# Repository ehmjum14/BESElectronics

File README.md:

# BESElectronics
Electronic part of the BESDyno diploma thesis
 - [Software part by Emil Berger](https://github.com/beremm14/BESDyno)

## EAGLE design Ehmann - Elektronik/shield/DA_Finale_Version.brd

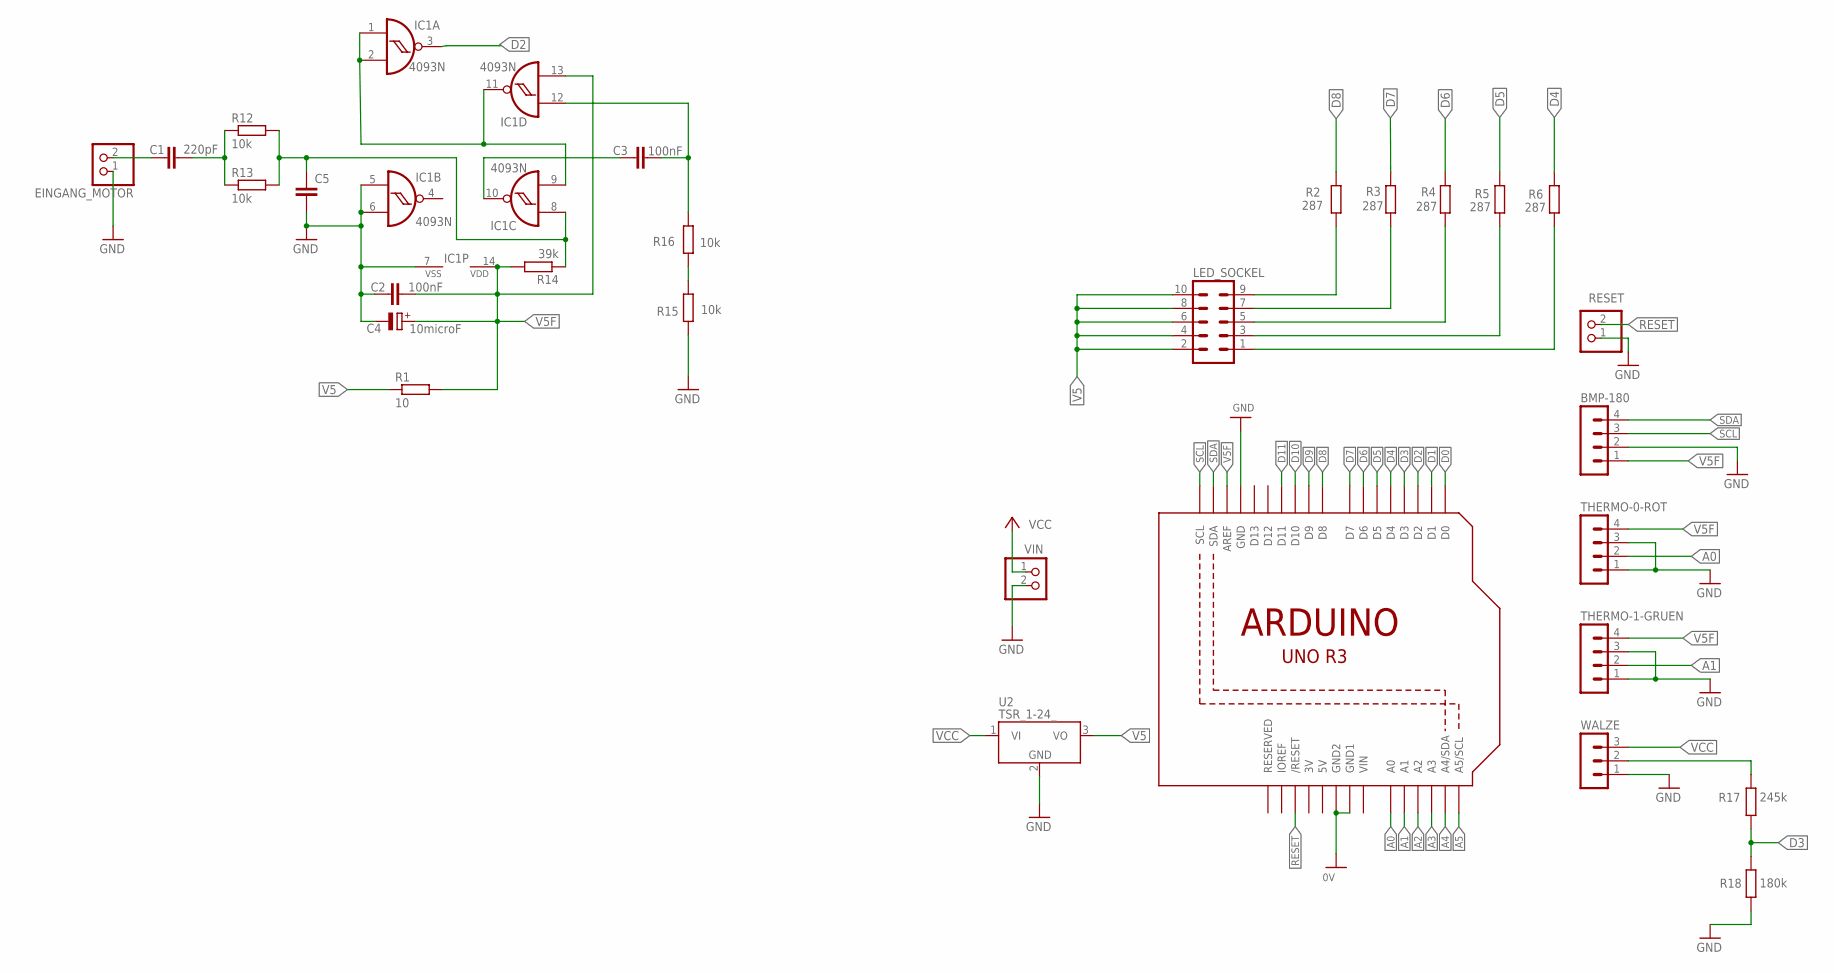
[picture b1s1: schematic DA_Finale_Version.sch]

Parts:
BMP-180: MA04-1
C1: 220pF; C050-025X075
C2, C3: 100nF; C050-025X075
C4: 10microF; E3,5-8
C5: C-EU050-025X075; C050-025X075
EINGANG_MOTOR: PINHD-1X2; 1X02
IC1: 4093N; DIL14
LED_SOCKEL: MA05-2
R1: 10; 0207/7
R2, R3, R4, R5, R6: 287; 0207/10
R12, R13, R15, R16: 10k; 0207/7
R14: 39k; 0207/7
R17: 245k; 0207/7
R18: 180k; 0207/7
RESET: PINHD-1X2; 1X02
THERMO-0-ROT, THERMO-1-GRUEN: MA04-1
U1: ARDUINOR3-BPLACE
U2: TSR_1-24_; TSR-1
VIN: PINHD-1X2; 1X02
WALZE: MA03-1

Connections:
3V: U1.3V
5V: U1.5V
A0: THERMO-0-ROT.2, U1.A0
A1: THERMO-1-GRUEN.2, U1.A1
A2: U1.A2
A3: U1.A3
A4: U1.A4 (A4/SDA)
A5: U1.A5 (A5/SCL)
D0: U1.D0
D1: U1.D1
D2: IC1.3 (O), U1.D2
D3: R17.1, R18.2, U1.D3
D4: R6.2, U1.D4
D5: R5.2, U1.D5
D6: R4.2, U1.D6
D7: R3.2, U1.D7
D8: R2.2, U1.D8
D9: U1.D9
D10: U1.D10
D11: U1.D11
GND: BMP-180.2, C2.1, C4.-, C5.2, EINGANG_MOTOR.1, IC1.5 (I0), IC1.6 (I1), IC1.7 (VSS), R15.1, R18.1, RESET.1, THERMO-0-ROT.1, THERMO-0-ROT.3, THERMO-1-GRUEN.1, THERMO-1-GRUEN.3, U1.GND, U1.GND1, U1.GND2, U2.2 (GND), VIN.2, WALZE.1
unnamed: LED_SOCKEL.9, R2.1
unnamed: LED_SOCKEL.7, R3.1
unnamed: LED_SOCKEL.5, R4.1
unnamed: LED_SOCKEL.3, R5.1
unnamed: LED_SOCKEL.1, R6.1
unnamed: C1.1, EINGANG_MOTOR.2
unnamed: C1.2, R12.1, R13.1
unnamed: C3.1, IC1.12 (I0), R16.2
unnamed: IC1.1 (I0), IC1.2 (I1), IC1.9 (I1), IC1.11 (O)
unnamed: R17.2, WALZE.2
unnamed: C5.1, IC1.8 (I0), R12.2, R13.2, R14.1
unnamed: R15.2, R16.1
unnamed: C3.2, IC1.10 (O)
RESET: RESET.2, U1.RESET (/RESET)
SCL: BMP-180.3, U1.SCL
SDA: BMP-180.4, U1.SDA
V5: LED_SOCKEL.2, LED_SOCKEL.4, LED_SOCKEL.6, LED_SOCKEL.8, LED_SOCKEL.10, R1.1, U2.3 (VO)
V5F: BMP-180.1, C2.2, C4.+, IC1.13 (I1), IC1.14 (VDD), R1.2, R14.2, THERMO-0-ROT.4, THERMO-1-GRUEN.4, U1.AREF
VCC: U2.1 (VI), VIN.1, WALZE.3
VIN: U1.VIN

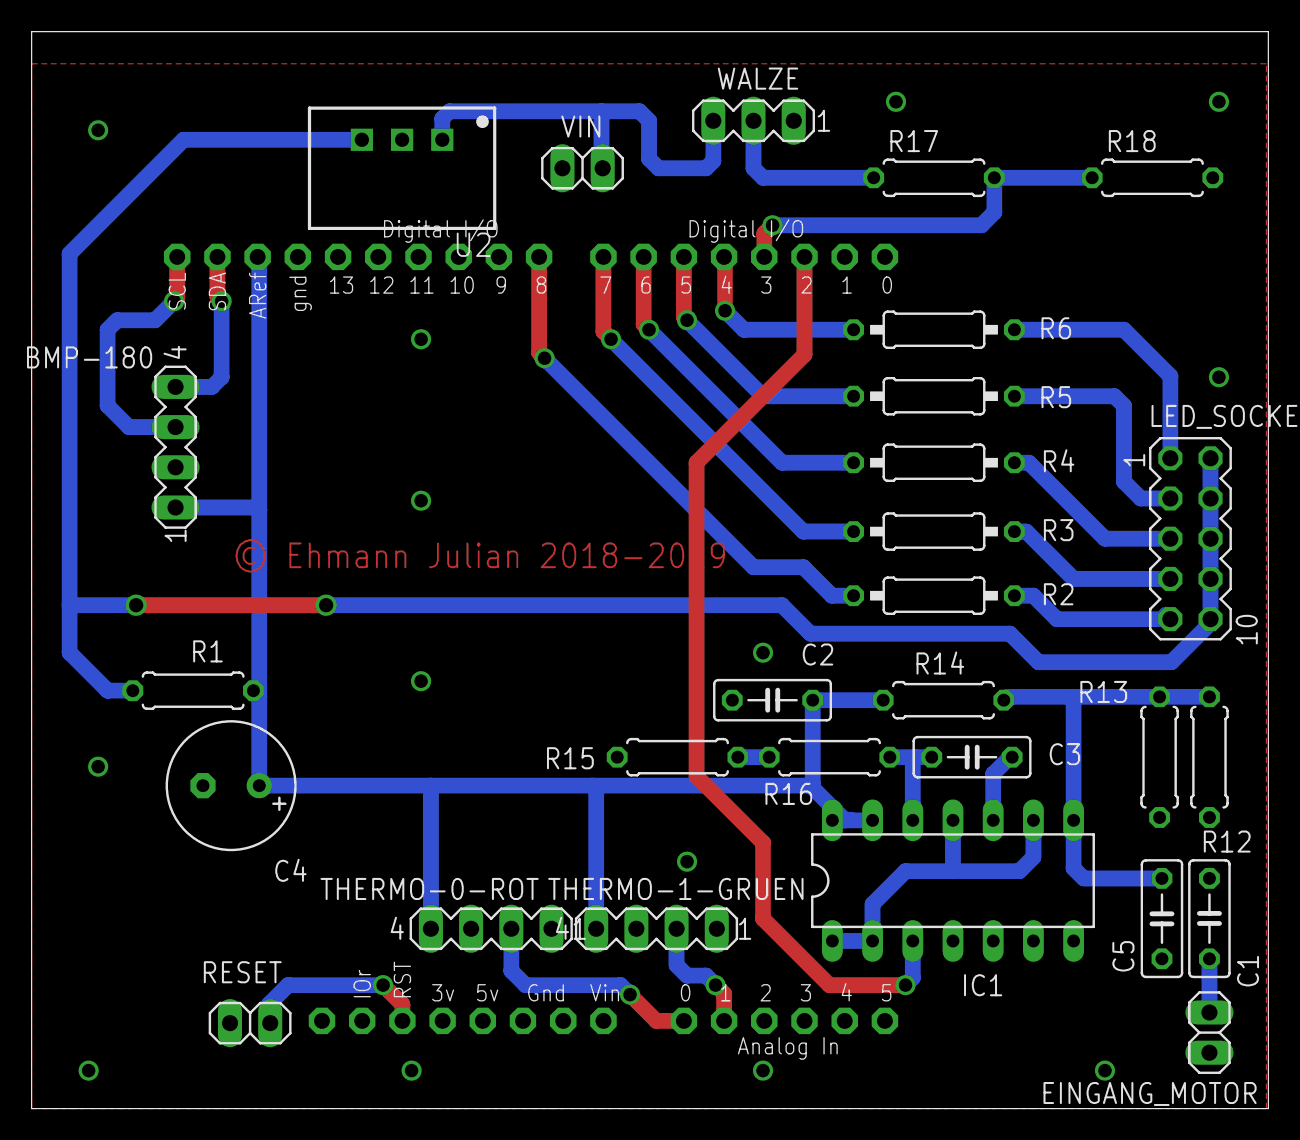
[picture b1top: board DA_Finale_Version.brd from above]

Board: 2 copper layers, 78.1 x 68.0 mm, 29 parts (0 on the bottom side), 29 nets.

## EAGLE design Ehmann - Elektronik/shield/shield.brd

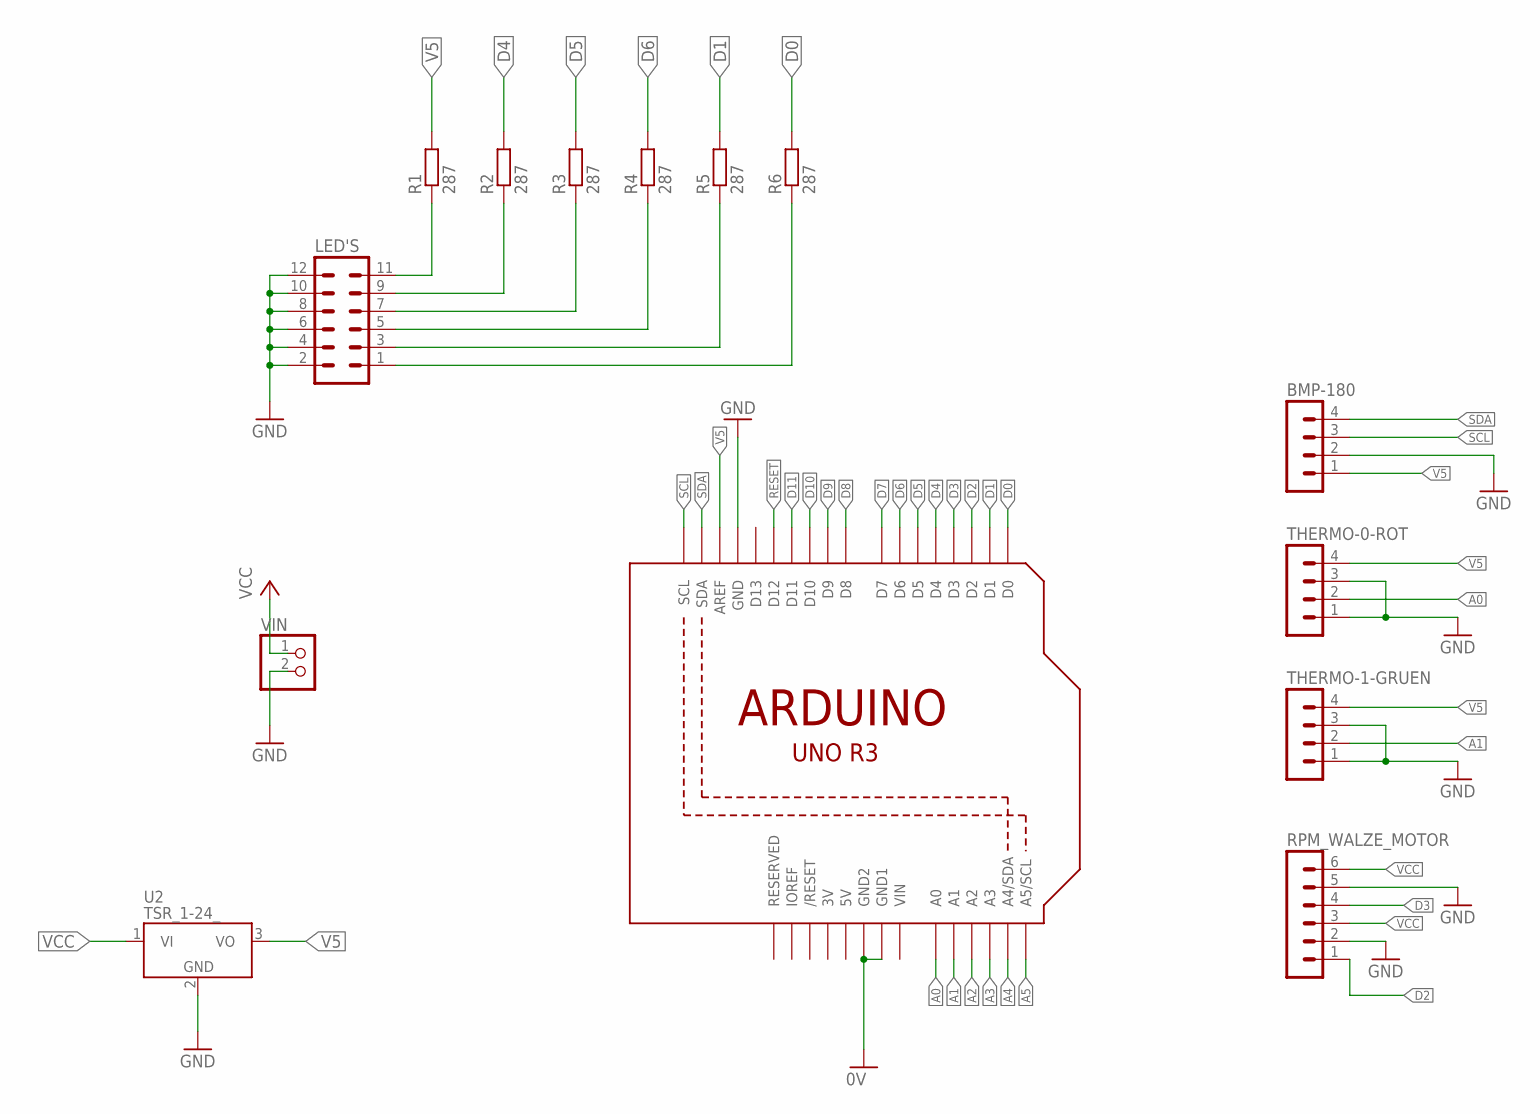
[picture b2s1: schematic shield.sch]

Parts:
BMP-180: MA04-1
LED'S: MA06-2
R1, R2, R3, R4, R5, R6: 287; 0207/10
RPM_WALZE_MOTOR: MA06-1
THERMO-0-ROT, THERMO-1-GRUEN: MA04-1
U1: ARDUINOR3-BPLACE
U2: TSR_1-24_; TSR-1
VIN: PINHD-1X2; 1X02

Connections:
3V: U1.3V
5V: U1.5V
A0: THERMO-0-ROT.2, U1.A0
A1: THERMO-1-GRUEN.2, U1.A1
A2: U1.A2
A3: U1.A3
A4: U1.A4 (A4/SDA)
A5: U1.A5 (A5/SCL)
D0: R6.2, U1.D0
D1: R5.2, U1.D1
D2: RPM_WALZE_MOTOR.1, U1.D2
D3: RPM_WALZE_MOTOR.4, U1.D3
D4: R2.2, U1.D4
D5: R3.2, U1.D5
D6: R4.2, U1.D6
D7: U1.D7
D8: U1.D8
D9: U1.D9
D10: U1.D10
D11: U1.D11
GND: BMP-180.2, LED'S.2, LED'S.4, LED'S.6, LED'S.8, LED'S.10, LED'S.12, RPM_WALZE_MOTOR.2, RPM_WALZE_MOTOR.5, THERMO-0-ROT.1, THERMO-0-ROT.3, THERMO-1-GRUEN.1, THERMO-1-GRUEN.3, U1.GND, U1.GND1, U1.GND2, U2.2 (GND), VIN.2
unnamed: LED'S.9, R2.1
unnamed: LED'S.7, R3.1
unnamed: LED'S.5, R4.1
unnamed: LED'S.3, R5.1
unnamed: LED'S.1, R6.1
unnamed: LED'S.11, R1.1
RESET: U1.D12
SCL: BMP-180.3, U1.SCL
SDA: BMP-180.4, U1.SDA
V5: BMP-180.1, R1.2, THERMO-0-ROT.4, THERMO-1-GRUEN.4, U1.AREF, U2.3 (VO)
VCC: RPM_WALZE_MOTOR.3, RPM_WALZE_MOTOR.6, U2.1 (VI), VIN.1
VIN: U1.VIN

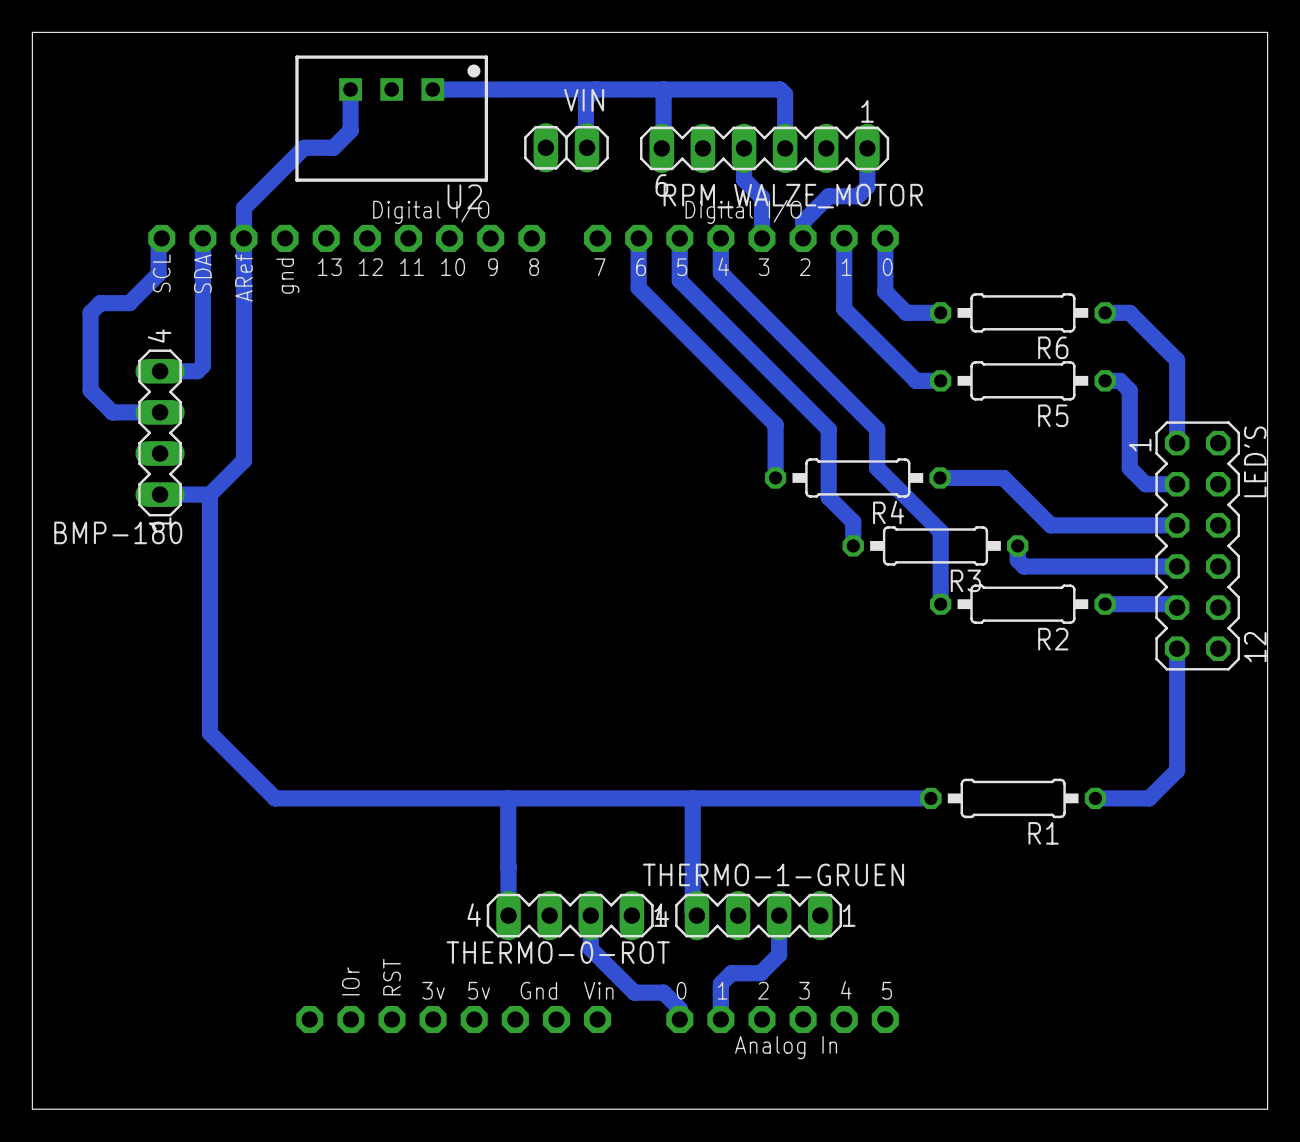
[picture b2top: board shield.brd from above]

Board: 2 copper layers, 76.3 x 66.5 mm, 14 parts (0 on the bottom side), 20 nets.

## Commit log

2019-04-05 Upload first version

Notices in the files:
Ehmann - Elektronik/shield/DA_Finale_Version.brd:
© Ehmann Julian 2018-2019
